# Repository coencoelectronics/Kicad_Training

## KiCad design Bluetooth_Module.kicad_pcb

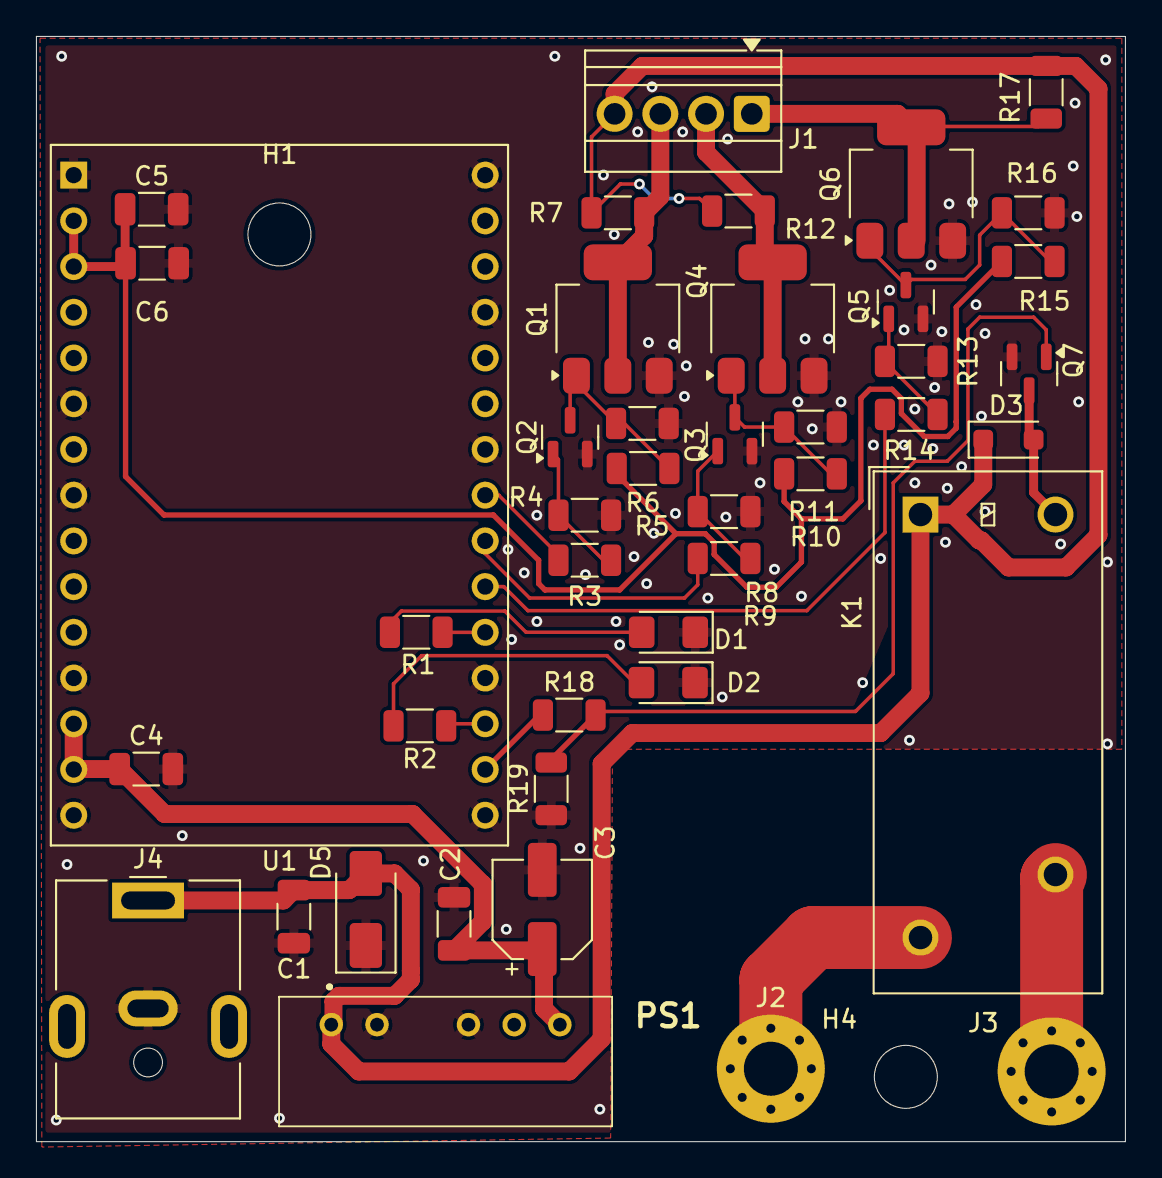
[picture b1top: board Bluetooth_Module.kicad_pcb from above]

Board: 2 copper layers, 60.5 x 61.4 mm, 45 parts (0 on the bottom side), 25 nets.

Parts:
C1, C2, C4, C5: 100n/25V; C_1206_3216Metric
C3: 22uF/35V; CP_Elec_5x5.8
C6: 1u/6V3; C_1206_3216Metric
D1: RED; LED_1206_3216Metric_Pad1.42x1.75mm_HandSolder
D2: GREEN; LED_1206_3216Metric_Pad1.42x1.75mm_HandSolder
D3: D; D_SOD-123F
D5: D_TVS_12V; D_SMA
H1, H4: MountingHole; MountingHole_3.5mm
J1: Conn_01x04_Pin; TerminalBlock_Xinya_XY308-2.54-4P_1x04_P2.54mm_Horizontal
J2, J3: Conn_01x01_Socket; MountingHole_3mm_Pad_Via
J4: Jack-DC; BarrelJack_CUI_PJ-063AH_Horizontal
K1: G2RL-1A-H; Relay_SPST_Omron_G2RL-1A
PS1: DPU01N-15; DPU01N15
Q1, Q4, Q6: STN3NF06; SOT-223-3_TabPin2
Q2, Q3, Q5, Q7: BC817; SOT-23
R1: 270R; R_1206_3216Metric
R2: 68R; R_1206_3216Metric
R3, R8, R13, R18: 1k; R_1206_3216Metric
R4, R5, R6, R9, R10, R11, R14, R15, R16, R19: 10k; R_1206_3216Metric
R7, R12, R17: 100k; R_1206_3216Metric
U1: ESP32-C3-DevKitM-1

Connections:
+3V3: C5.1, C6.1, R5.2, R10.2, R15.2, U1.2 (3V3), U1.3 (3V3)
+5V: C2.1, C3.1, C4.1, PS1.6 (+VOUT), U1.13 (5V), U1.14 (5V)
+12V: C1.1, D3.1 (K), D5.2 (A2), J1.4, J4.1, K1.A1, PS1.1 (+VIN), R7.2, R12.2, R17.2
GND: C1.2, C2.2, C3.2, C4.2, C5.2, C6.2, D1.1 (K), D2.1 (K), D5.1 (A1), J4.2, PS1.2 (-VIN), PS1.4 (-VOUT), Q1.3 (S), Q2.2 (E), Q3.2 (E), Q4.3 (S), Q5.2 (E), Q6.3 (S), Q7.2 (E), R4.1, R6.1, R9.1, R11.1, R14.1, R16.1, R19.1, U1.1 (GND), U1.6 (GND), U1.8 (GND), U1.12 (GND), U1.15 (GND), U1.16 (GND), U1.19 (GND), U1.24 (GND), U1.27 (GND), U1.30 (GND)
LED_B: R13.1, U1.21 (IO5)
LED_B_OUT: J1.1, Q6.2 (D), R17.1
LED_G: R8.1, U1.22 (IO6)
LED_G_OUT: J1.2, Q4.2 (D), R12.1
LED_R: R3.1, U1.23 (IO7)
LED_R_OUT: J1.3, Q1.2 (D), R7.1
unnamed: D1.2 (A), R1.2
unnamed: D2.2 (A), R2.2
unnamed: D3.2 (A), K1.A2, Q7.3 (C)
unnamed: J2.1, K1.14
unnamed: J3.1, K1.13
unnamed: Q1.1 (G), Q2.3 (C), R5.1, R6.2
unnamed: Q2.1 (B), R3.2, R4.2
unnamed: Q3.1 (B), R8.2, R9.2
unnamed: Q3.3 (C), Q4.1 (G), R10.1, R11.2
unnamed: Q5.1 (B), R13.2, R14.2
unnamed: Q5.3 (C), Q6.1 (G), R15.1, R16.2
unnamed: Q7.1 (B), R18.2, R19.2
unnamed: R1.1, U1.20 (IO4)
unnamed: R2.1, U1.18 (IO18)
RELAY: R18.1, U1.17 (IO19)

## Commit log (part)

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2026-03-19 Lesson 1 - base established
2026-03-19 Lesson 2 - transistor circuits added
2026-04-23 Lesson 4 - Power Supply
